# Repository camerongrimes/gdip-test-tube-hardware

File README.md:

# GDIP Test Tube Hardware

Controller for AL5D Lynxmotion robotic arm.

## Features

- Webpage based more control using WiFi from the ESP32.
- Six servo outputs for control of all AL5D servos.
- Buzzer used to warn user that robotic arm is about to move.
- Seven segment display for error codes.
- Extra screw terminal for control of safety lightings around the arm.

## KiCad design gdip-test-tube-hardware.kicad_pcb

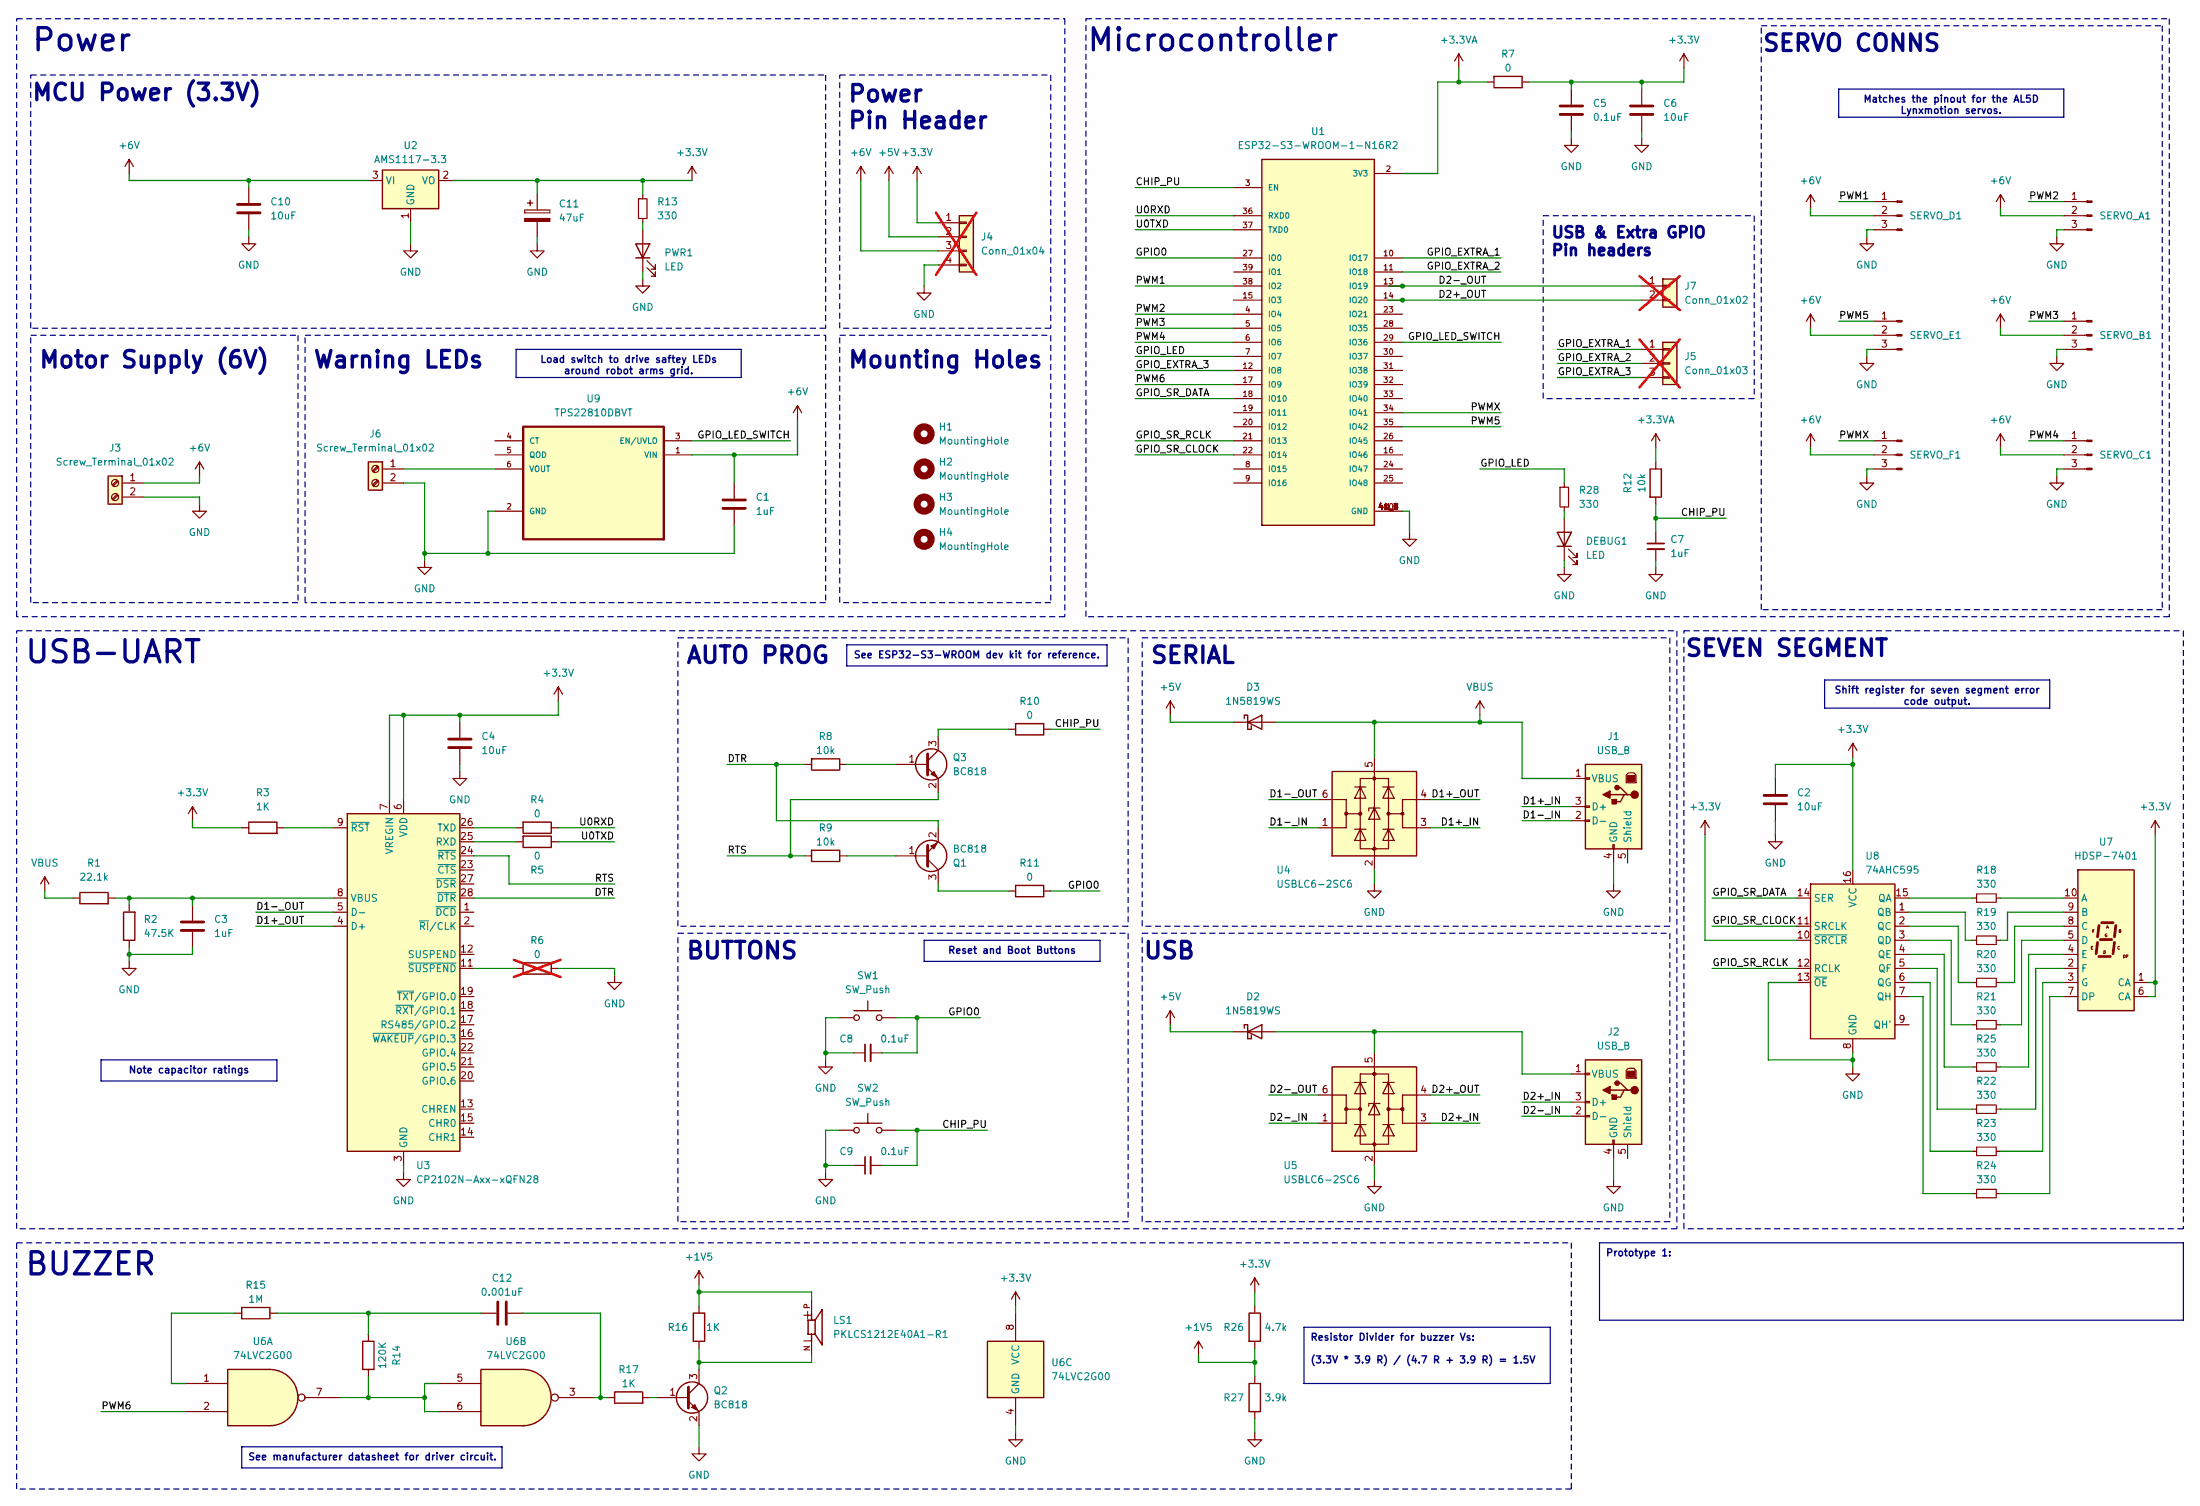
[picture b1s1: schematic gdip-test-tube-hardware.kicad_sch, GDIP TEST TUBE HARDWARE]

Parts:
C1, C3, C7: 1uF; C_0805_2012Metric
C2, C4, C6, C10: 10uF; C_0805_2012Metric
C5, C8, C9: 0.1uF; C_0805_2012Metric
C11: 47uF; CAP_EEEHA1H470XP
C12: 0.001uF; C_0805_2012Metric
D2, D3: 1N5819WS; D_SOD-323
DEBUG1: LED; LED_0805_2012Metric
H1, H2, H3, H4: MountingHole; MountingHole_3.5mm
J1, J2: USB_B; USB_Mini-B_Wuerth_65100516121_Horizontal
J3, J6: Screw_Terminal_01x02; TE_282837-2
J4: Conn_01x04; PinHeader_1x04_P2.54mm_Vertical; not fitted
J5: Conn_01x03; PinHeader_1x03_P2.54mm_Vertical; not fitted
J7: Conn_01x02; PinHeader_1x02_P2.54mm_Vertical; not fitted
LS1: PKLCS1212E40A1-R1; SPKR_PKLCS1212E40A1-R1; PARTREV January 22, 2018
PWR1: LED; LED_0805_2012Metric
Q1, Q2, Q3: BC818; SOT-23
R1: 22.1k; R_0805_2012Metric
R2: 47.5K; R_0805_2012Metric
R3, R16, R17: 1K; R_0805_2012Metric
R4, R5, R7, R10, R11: 0; R_0805_2012Metric
R6: 0; R_0805_2012Metric; not fitted
R8, R9, R12: 10k; R_0805_2012Metric
R13, R18, R19, R20, R21, R22, R23, R24, R25, R28: 330; R_0805_2012Metric
R14: 120K; R_0805_2012Metric
R15: 1M; R_0805_2012Metric
R26: 4.7k; R_0805_2012Metric
R27: 3.9k; R_0805_2012Metric
SERVO_A1: Conn_01x03_Pin; FanPinHeader_1x03_P2.54mm_Vertical
SERVO_B1: Conn_01x03_Pin; FanPinHeader_1x03_P2.54mm_Vertical
SERVO_C1: Conn_01x03_Pin; FanPinHeader_1x03_P2.54mm_Vertical
SERVO_D1: Conn_01x03_Pin; FanPinHeader_1x03_P2.54mm_Vertical
SERVO_E1: Conn_01x03_Pin; FanPinHeader_1x03_P2.54mm_Vertical
SERVO_F1: Conn_01x03_Pin; FanPinHeader_1x03_P2.54mm_Vertical
SW1, SW2: SW_Push; SW_PUSH_6mm
U1: ESP32-S3-WROOM-1-N16R2; XCVR_ESP32-S3-WROOM-1-N16R2; PARTREV v1.0
U2: AMS1117-3.3; SOT-223-3_TabPin2
U3: CP2102N-Axx-xQFN28; QFN-28-1EP_5x5mm_P0.5mm_EP3.35x3.35mm
U4: USBLC6-2SC6; SOT-23-6; JLCPCB C2687116
U5: USBLC6-2SC6; SOT-23-6
U6: 74LVC2G00; VSSOP-8_2.4x2.1mm_P0.5mm
U7: HDSP-7401
U8: 74AHC595; SOIC-16_3.9x9.9mm_P1.27mm
U9: TPS22810DBVT; SOT95P280X145-6N

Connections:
+1V5: LS1.P, R16.1, R26.2, R27.1
+3.3V: C2.1, C4.1, C5.1, C6.1, C11.1, J4.1, R3.1, R7.1, R13.1, R26.1, U2.2 (VO), U3.6 (VDD), U3.7 (VREGIN), U6.8 (VCC), U7.1 (CA), U7.6 (CA), U8.10 (~SRCLR), U8.16 (VCC)
+3.3VA: R7.2, R12.1, U1.2 (3V3)
+5V: D2.1 (K), D3.1 (K), J4.2
+6V: C1.1, C10.1, J3.1, J4.3, SERVO_A1.2, SERVO_B1.2, SERVO_C1.2, SERVO_D1.2, SERVO_E1.2, SERVO_F1.2, U2.3 (VI), U9.1 (VIN)
/CHIP_PU: C7.1, C9.2, R10.1, R12.2, SW2.2, U1.3 (EN)
/D1+_IN: J1.3 (D+), U4.3 (I/O2)
/D1+_OUT: U3.4 (D+), U4.4 (I/O2)
/D1-_IN: J1.2 (D-), U4.1 (I/O1)
/D1-_OUT: U3.5 (D-), U4.6 (I/O1)
/D2+_IN: J2.3 (D+), U5.3 (I/O2)
/D2+_OUT: J7.2, U1.14 (IO20), U5.4 (I/O2)
/D2-_IN: J2.2 (D-), U5.1 (I/O1)
/D2-_OUT: J7.1, U1.13 (IO19), U5.6 (I/O1)
/DTR: Q1.2 (E), R8.2, U3.28 (~DTR)
/GPIO0: C8.2, R11.1, SW1.2, U1.27 (IO0)
/GPIO_EXTRA_1: J5.1, U1.10 (IO17)
/GPIO_EXTRA_2: J5.2, U1.11 (IO18)
/GPIO_EXTRA_3: J5.3, U1.12 (IO8)
/GPIO_LED: R28.1, U1.7 (IO7)
/GPIO_LED_SWITCH: U1.29 (IO36), U9.3 (EN/UVLO)
/GPIO_SR_CLOCK: U1.22 (IO14), U8.11 (SRCLK)
/GPIO_SR_DATA: U1.18 (IO10), U8.14 (SER)
/GPIO_SR_RCLK: U1.21 (IO13), U8.12 (RCLK)
/PWM1: SERVO_D1.1, U1.38 (IO2)
/PWM2: SERVO_A1.1, U1.4 (IO4)
/PWM3: SERVO_B1.1, U1.5 (IO5)
/PWM4: SERVO_C1.1, U1.6 (IO6)
/PWM5: SERVO_E1.1, U1.35 (IO42)
/PWM6: U1.17 (IO9), U6.2
/PWMX: SERVO_F1.1, U1.34 (IO41)
/RTS: Q3.2 (E), R9.2, U3.24 (~RTS)
/U0RXD: R4.1, U1.36 (RXD0)
/U0TXD: R5.1, U1.37 (TXD0)
GND: C1.2, C2.2, C3.2, C4.2, C5.2, C6.2, C7.2, C8.1, C9.1, C10.2, C11.2, DEBUG1.1 (K), J1.4 (GND), J2.4 (GND), J3.2, J4.4, J6.2, PWR1.1 (K), Q2.2 (E), R2.1, R6.1, R27.2, SERVO_A1.3, SERVO_B1.3, SERVO_C1.3, SERVO_D1.3, SERVO_E1.3, SERVO_F1.3, SW1.1, SW2.1, U1.1 (GND), U1.40 (GND), U1.41_1 (GND), U1.41_2 (GND), U1.41_3 (GND), U1.41_4 (GND), U1.41_5 (GND), U1.41_6 (GND), U1.41_7 (GND), U1.41_8 (GND), U1.41_9 (GND), U2.1 (GND), U3.3 (GND), U3.29 (GND), U4.2 (GND), U5.2 (GND), U6.4 (GND), U8.8 (GND), U8.13 (~OE), U9.2 (GND)
unnamed: C12.1, R14.1, R15.1
unnamed: C12.2, R17.1, U6.3
unnamed: D2.2 (A), J2.1 (VBUS), U5.5 (VBUS)
unnamed: DEBUG1.2 (A), R28.2
unnamed: J6.1, U9.6 (VOUT)
unnamed: PWR1.2 (A), R13.2
unnamed: Q1.1 (B), R9.1
unnamed: Q1.3 (C), R11.2
unnamed: Q2.1 (B), R17.2
unnamed: LS1.N, Q2.3 (C), R16.2
unnamed: Q3.1 (B), R8.1
unnamed: Q3.3 (C), R10.2
unnamed: R14.2, U6.5, U6.6, U6.7
unnamed: R15.2, U6.1
unnamed: R5.2, U3.25 (RXD)
unnamed: R4.2, U3.26 (TXD)
unnamed: C3.1, R1.2, R2.2, U3.8 (VBUS)
unnamed: R3.2, U3.9 (~RST)
unnamed: R6.2, U3.11 (~SUSPEND)
unnamed: R18.2, U7.10 (A)
unnamed: R19.2, U7.9 (B)
unnamed: R20.2, U7.8 (C)
unnamed: R21.2, U7.5 (D)
unnamed: R24.2, U7.7 (DP)
unnamed: R25.2, U7.4 (E)
unnamed: R22.2, U7.2 (F)
unnamed: R23.2, U7.3 (G)
unnamed: R18.1, U8.15 (QA)
unnamed: R19.1, U8.1 (QB)
unnamed: R20.1, U8.2 (QC)
unnamed: R21.1, U8.3 (QD)
unnamed: R25.1, U8.4 (QE)
unnamed: R22.1, U8.5 (QF)
unnamed: R23.1, U8.6 (QG)
unnamed: R24.1, U8.7 (QH)
VBUS: D3.2 (A), J1.1 (VBUS), R1.1, U4.5 (VBUS)

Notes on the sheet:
Shift register for seven segment error code output.
Matches the pinout for the AL5D Lynxmotion servos.
Load switch to drive saftey LEDs around robot arms grid.
Prototype 1:
Note capacitor ratings
Resistor Divider for buzzer Vs: (3.3V * 3.9 R) / (4.7 R + 3.9 R) = 1.5V
See ESP32-S3-WROOM dev kit for reference.
Reset and Boot Buttons
See manufacturer datasheet for driver circuit.
BUZZER
SERVO CONNS
SERIAL
USB
SEVEN SEGMENT
Microcontroller
Mounting Holes
AUTO PROG
Power Pin Header
Motor Supply (6V)
Warning LEDs
BUTTONS
Power
MCU Power (3.3V)
USB-UART
USB & Extra GPIO Pin headers

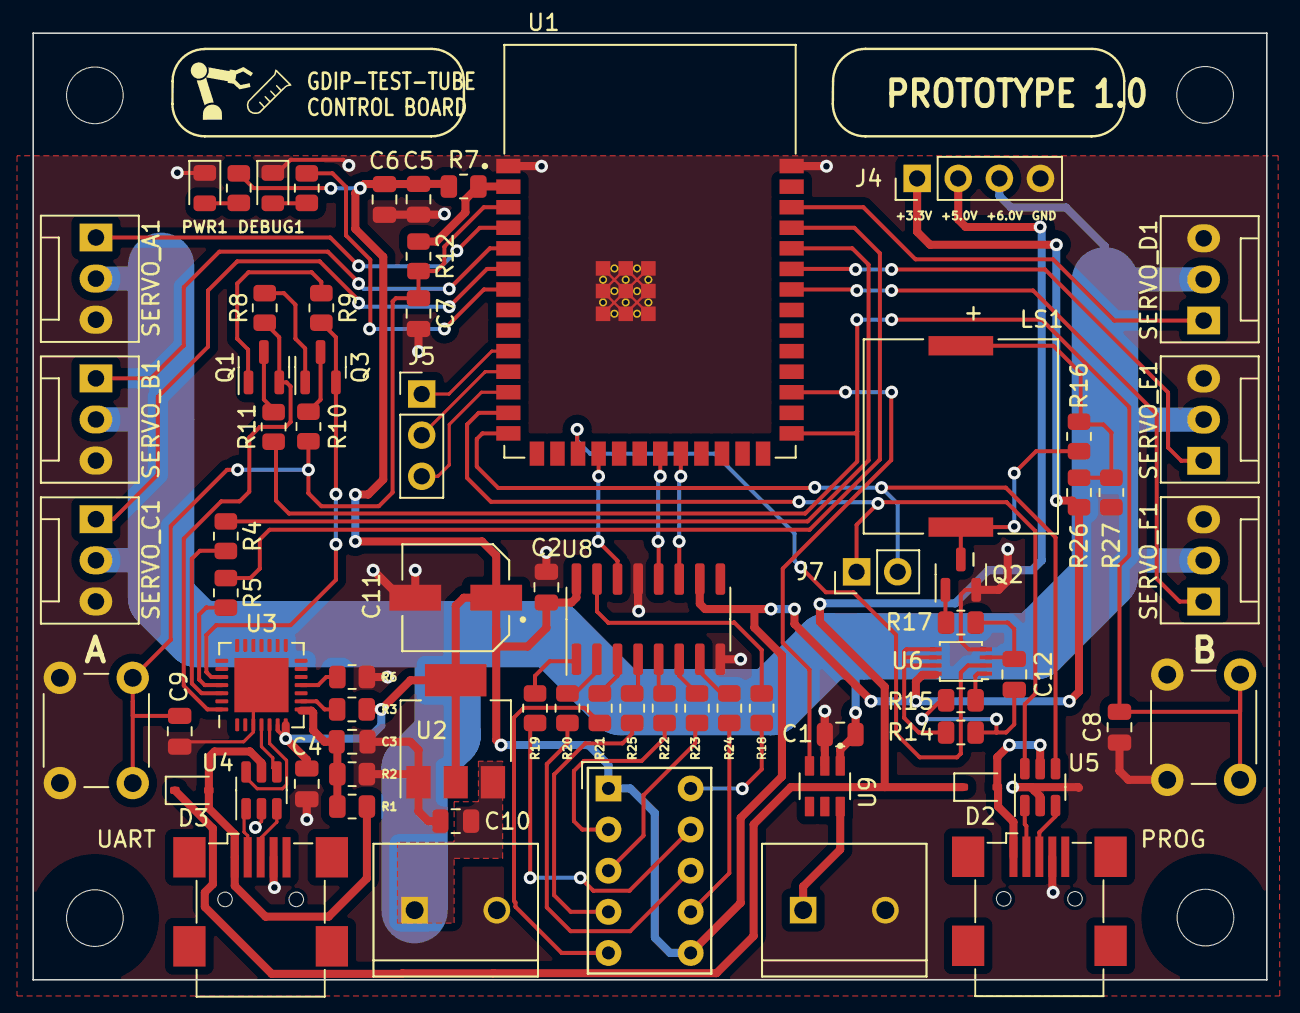
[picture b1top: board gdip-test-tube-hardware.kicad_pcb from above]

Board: 2 copper layers, 76.2 x 58.5 mm, 76 parts (0 on the bottom side), 71 nets.

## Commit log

2023-11-03 Added local lib for symbols and footprints. Added ESP32-S3-WROOM and folder for step models.
2023-11-05 Added in USB-UART IC
2023-11-07 Started adding in USB & ESD protection,
2023-11-14 Added connections for servo and finshed up usb-serial ic.
2023-11-14 Added auto prog circuit.
2023-11-14 Added pinout and connect pwm to servo pin header.
2023-11-14 Finshed switch cricuit for prog.
2023-11-14 Added caps for 3.3V reg and added nets for motor power supply.
2023-11-14 Added LED for power supply indication.
2023-11-14 Started inital layout, board with correct height and width, and main components placed.
2023-11-16 Added buzzer circuit in.
2023-11-22 Removed multiplexer for buzzer and servo as we can remap any ESP32 pin. Also switched mux for shift register for the 7-seg display.
2023-11-27 Further work on layout.
2023-11-28 Finished first layout added load switch for led saftey circuit,changed 47uF cap footprint. Also added extra pin headers for USB, Voltages & Gnd on board and extra GPIOs.
2023-11-28 Cleaned up files. Also have no DRC errors, had to make some changes to ESP32 thermal ties as they would not be within JLCPCB specs for a 2 layer board, hole size and pad were increased.
2023-11-28 Added custom symbols that are used in this project back in, this is a local file.
2023-11-28 Moved PWR led and added a DEBUG led in better locations. Also tested the step file of a molex part for servro headers.
2023-11-29 Reviewed schematic and made changes please view docs folder for more info. Schematic now complete.
2023-11-29 Inital DRC check all complete, now doing final run over.
